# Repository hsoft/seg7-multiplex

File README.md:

# Multiplexed 7-segment display array

This board is a multiplexed array of 4 7-segment displays that receives its
input through a custom serial protocol. The board uses a USB-A connector to
connect `VCC`, `GND` and its two serial pins. It's multiplexed to minimize the
number of pins and ICs we need to use. We end up only needing an ATtiny45 and
2 ICs to drive the 4 displays.

The goal is to be able to offload the "digit display" complexity off little
devices I'm planning to do. Of course, there's tons of ready-to-use displays
out there but I'd like to explore simple and minimal designs.

I'm also hoping to have something that draws minimal current. My current
prototype (v3) works on 3V and draws about 7mA when it's not receiving data. For
reference, the backlight of a typical 2x8 LCD screen draws something like
20-40mA.

Click on the image below for a video:

## Serial protocol

It works by serially sending it 5 bits of data using `INSER` and `INCLK`, the
first 4 bits being an encoded digit from `0` to `9`. Each digit is sent
starting with the most significant bit. Before each digit, a single bit is sent
to indicate whether this digit has a dot. The first digit to be sent is the
least significant digit (the rightmost).

Before that, a single "empty" clock is sent to "wake" the MCU up and give it
time to put itself in "input" mode (that is, give it time to finish its current
refresh operation, if any).

The driver should wait 200us before the "wake up" trigger and the rest of the
data so that we have time to finish any ongoing display refresh operation.
after that, 50us between each clock should be enough.

Thus, to send "43.21", the bits to be sent would be:

    00100 (4)
    10011 (dot + 3)
    00010 (2)
    00001 (1)
    01010 (10, the checksum of 4 + 3 + 2 + 1)

This is done for each digit that needs to be shown (starting with the rightmost
digit). This means 20 bits.

Following that, we have a checksum which is the sum, in binary form, of the
sent digits. That sum is 5 bits long. It's not enough to hold the maximum value
(36) of that sum, but being 5 bits simplifies the code and is solid enough for
our purpose. Dot masks aren't checksummed.

If the checksum doesn't match the received number, the display shows an error
that can't be mistaken for a real number.

I could have gone for sending straight binary values instead of digits but I
thought it would be nice to eventually add support for special values (dash,
empty, etc)

The board itself takes care of properly refreshing the displays. We refresh one
display every 1ms, cycling over active displays. We only need to send new digits
when they change.

## Prototypes

### v1

My first prototype was using two shift registers to multiplex my 7-segments
digits. It worked rather well but my craftmanship was lacking. Soldering wasn't
good and the board was too cramped. I also forgot (or didn't know about) to add
decoupling capacitors next to my ICs and I think that this is why that prototype
wasn't working perfectly (it would receive the wrong data through serial and
would even sometimes have a corrupt display (missing/extra segment) about 10% of
the time). Also, to get that figure to 10% from 50%, I had to lower my serial
clock timing to 100us (a minimum of 100us between serial clocks). That seems a
bit high to me. Something is fishy.

As a software developer, I'm used to be on solid grounds. If the code is
logical, generally, things work. Here I have to learn to deal with timing and
power fluctuation issues. These present interesting challenges.

Because my board was too cramped, I needed to make a new prototype altogether
(with decoupling capacitors this time) and I thought that if I was going to do
that, I might as well try another design, that is, my v2.

You can see the code for this v1 in the `v1` branch of this repo. I have no
KiCAD schema though. Never bothered. Will do for v2 though.

### v2

Although I think that my design for v1 was globally sound, I think in
retrospective that the MCU did too many things. The less things the MCU does,
the more logic you offload to ICs, the more robust your design is going to be (I
think). After all, people designing ICs went through much more trouble to make
sure it worked well than I did for my prototype...

So that's why I went with a new multiplex design with 3 ICs:

1. 7-segment decoder hooked to my displays
2. binary counter hooked to the decoder
3. shift register hooked to displays' `VCC` (and `DP`)

With the decoder + counter, sending a particular digit mask to the display is
only a matter of clocking the counter, so it's only two pin changes. That is
much much less than the number of pins we have to change to send a particular
digit mask into a shift register.

I could use a decade counter to only cycle through the first 10 glyphs of my
decoder's 16, but as I looked as extra glyphs, I realized (I really wasn't sure
what they were supposed to be for initially) that they're probably optimized for
multiplexing, that is, that the 5 extra masks (last one is blank) are masks that
"fit" multiple digits. For example, the 11th mask is the lower half of `5` which
also fits 6 and 8.

Therefore, when cycling through masks, you can enable `VCC` not only for exact
digit matches but also partial matches and, in the end, you've refreshed your
multiplexed displays properly. I'm thinking that 1ms per cycle should be good
enough to keep us under the 10ms threshold (at which point the eye starts to see
a flicker) even if we cycle through 16 digit masks.

One problem though is that the 7-segments decoder doesn't handle `DP`, which I'd
like to support. This is why I'm thinking of bringing down (theoretical) digit
support from 8 to 4 and hook 4 pins of my shift register directly to my `DP`
pins. This way, I'll handle `DP` status completely outside of the multiplexing
process.

With the `ATtiny45`, I only have 3 free output pins (2 pins are used for serial
communication). That requires creativity to handle all my ICs with only 3 pins,
but I think I have a good idea:

1. pins 1 and 2 hooked to my shift register
2. pin 3 to my binary counter
3. pin 3 also hooked to my shift register's `OE` pin (output enable).

I need to control `OE` because there's always going to be a slight window of
time during which the decoder cycled and the shift register hasn't updated `VCC`
pin yet. If I let `OE` on, then my displays are going to have "ghost" branches.
The pin clocking the binary counter is going to be in position to enable `OE`
most of the time and right when we will toggle the binary counter clock, `OE`
will become disabled. Then, I'll update the shift register and toggle `OE` back
(which will not trigger a binary counter update since it takes a full on/off
cycle to trigger). I haven't looked yet whether I'm going to be needing an
inverter for this. If yes, I'll probably look for a shift register that allows
me to do that without an inverter (an extra IC just for this seem a bit much).

**Conclusion**: It went well! It was the first time I ordered a PCB from a
KiCAD design. Of course, I made some mistakes in it and a lot of cowboy
soldering was necessary to adjust, but in the end, I had a fully functional
prototype! Unlike v1, it received data properly and displayed it correctly!

However, I'm not done yet, I need a v3 because 3 ICs is too many: I'd like to
get this package in a 55mmx30mmx20mm enclosure. I'll need to go "double side"
and remove an IC.

### v3

With v3, I get rid of the counter. Instead of using 4 bits of the SR for DP,
I connect them to the BCD. Then, I connect SER to DP add a refresh "round"
especially for DP. This means that we generally have to keep SER high to avoid
falsely lighting DPs.

It still offloads most of the complexity to the BCD and gets rid of an IC.
Moreover, althrough I didn't experience it, I felt that the CNT approach was
flaky: the counter **had** to stay in sync with the MCU and the MCU had no way
to reset the counter to enforce syncing (not enough pins).

## Build

To build the software, you need:

* [AVRA][avra]
* [avrdude][avrdude] to send firmware to MCUs

You can build the resulting `seg7multiplex.S.hex` with `make` and send it to
the MCU through `avrdude` with `make send`.

## Simulation

This project can be run on a desktop computer through [simavr][simavr]. It 
produces a VCD file which can then be opened with [gtkwave][gtkwave].

You can compile the simulation with `make simulation` and then run the
resulting executable without parameters.

The simulation runs two MCUs at the same time. First, of course, the
`seg7multiplex` program, but also, on a separate virtual attiny45, the `drive`
program. It hooks them up together and let them run for 2 seconds.

The resulting gtkwave file is very insightful for debugging.

[avra]: http://avra.sourceforge.net/
[avrdude]: https://www.nongnu.org/avrdude/
[simavr]: https://github.com/buserror/simavr
[gtkwave]: http://gtkwave.sourceforge.net/

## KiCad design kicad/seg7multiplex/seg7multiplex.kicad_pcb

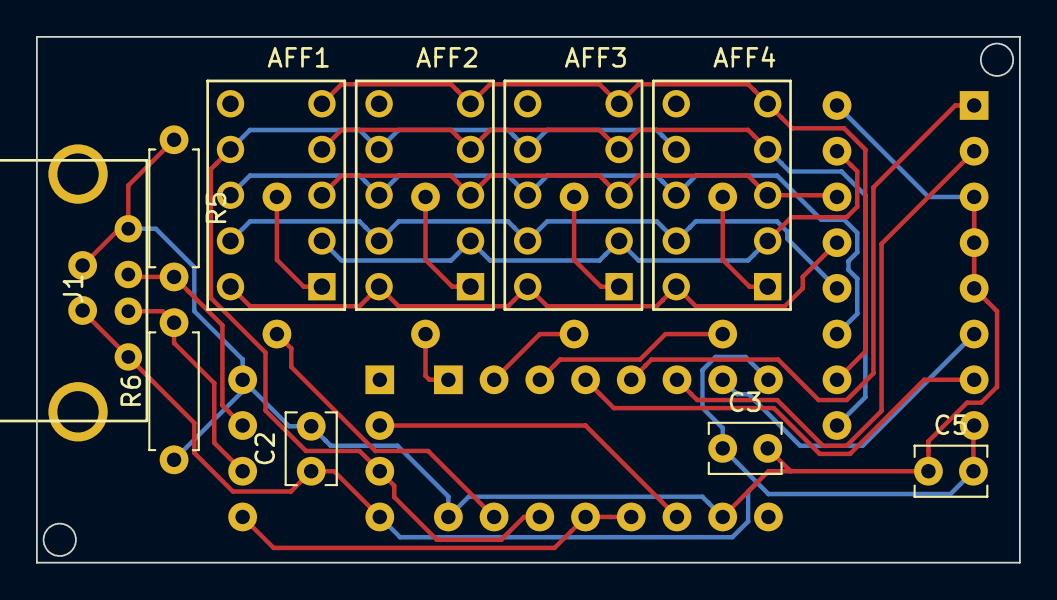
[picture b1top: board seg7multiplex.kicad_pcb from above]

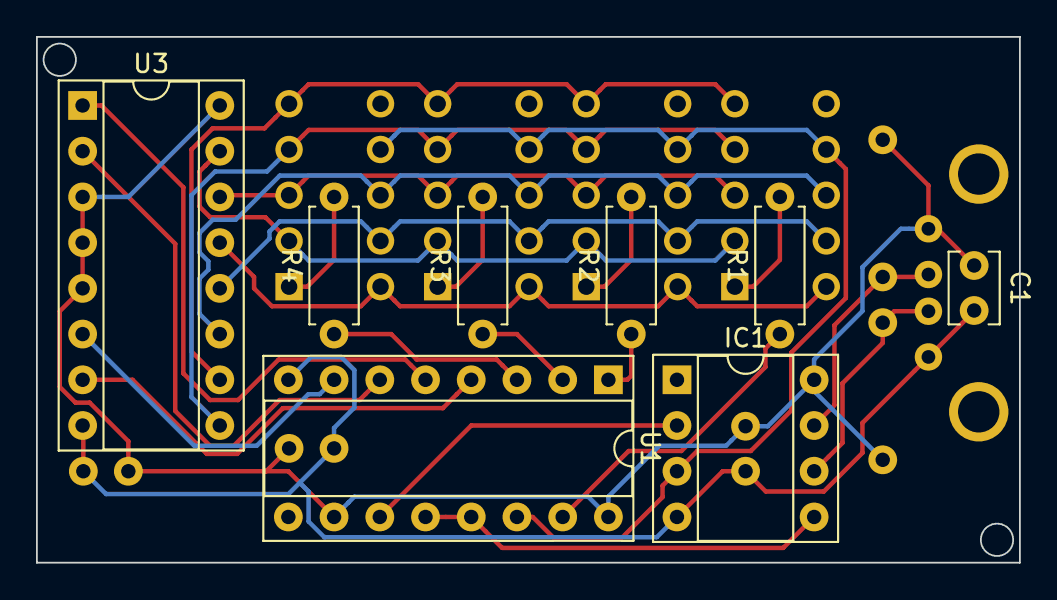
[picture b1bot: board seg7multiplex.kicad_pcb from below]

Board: 2 copper layers, 54.6 x 29.2 mm, 18 parts (8 on the bottom side), 26 nets.

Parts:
AFF1, AFF2, AFF3, AFF4: LSHD-A101
C1: 1uF; C_Disc_D3.8mm_W2.6mm_P2.50mm
C2, C3, C5: 0.1uF; C_Disc_D3.8mm_W2.6mm_P2.50mm
IC1: ATTINY45-P; DIP-8_W7.62mm_Socket
J1: USB_A; USB_A_Through
R1, R2, R3, R4: 110; R_Axial_DIN0207_L6.3mm_D2.5mm_P7.62mm_Horizontal
R5, R6: 10K; R_Axial_DIN0207_L6.3mm_D2.5mm_P7.62mm_Horizontal
U1: SN74HC595; DIP-16_W7.62mm_Socket
U3: 74LS48; DIP-16_W7.62mm_Socket

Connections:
/AFF1: R1.1, U1.15
/AFF2: R2.1, U1.1
/AFF3: R3.1, U1.2
/AFF4: R4.1, U1.3
/DECA: U1.4, U3.7
/DECB: U1.5, U3.1
/DECC: U1.6, U3.2
/DECD: U1.7, U3.6
/INCLK: IC1.7, J1.2, R5.2
/INSER: IC1.6, J1.3, R6.2
/RCLK: IC1.5, U1.12, U1.13
/SER_DP: AFF1.7, AFF2.7, AFF3.7, AFF4.7, IC1.3, U1.14
/SRCLK: IC1.2, U1.11
/a: AFF1.10, AFF2.10, AFF3.10, AFF4.10, U3.13
/b: AFF1.9, AFF2.9, AFF3.9, AFF4.9, U3.12
/c: AFF1.8, AFF2.8, AFF3.8, AFF4.8, U3.11
/d: AFF1.5, AFF2.5, AFF3.5, AFF4.5, U3.10
/e: AFF1.4, AFF2.4, AFF3.4, AFF4.4, U3.9
/f: AFF1.2, AFF2.2, AFF3.2, AFF4.2, U3.15
/g: AFF1.3, AFF2.3, AFF3.3, AFF4.3, U3.14
GND: C1.2, C2.1, C3.1, C5.2, IC1.4, J1.4, U1.8, U3.8
unnamed: AFF1.1, R1.2
unnamed: AFF2.1, R2.2
unnamed: AFF3.1, R3.2
unnamed: AFF4.1, R4.2
VCC: C1.1, C2.2, C3.2, C5.1, IC1.8, J1.1, R5.1, R6.1, U1.10, U1.16, U3.3, U3.4, U3.5, U3.16

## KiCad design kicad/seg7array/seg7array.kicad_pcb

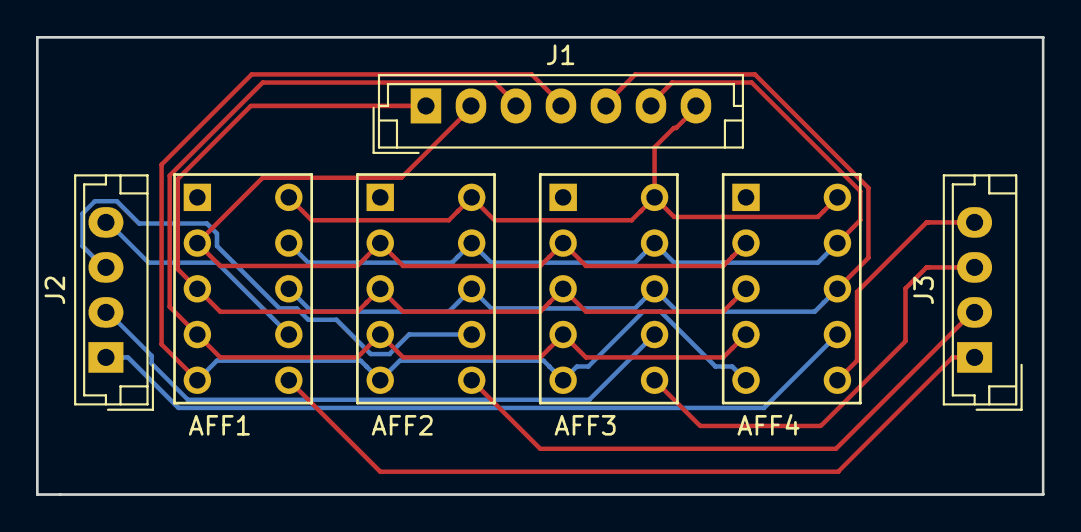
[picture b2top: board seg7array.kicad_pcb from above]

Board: 2 copper layers, 55.9 x 25.4 mm, 7 parts (0 on the bottom side), 15 nets.

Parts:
AFF1, AFF2, AFF3, AFF4: LSHD-A101
J1: Conn_01x07; JST_EH_B07B-EH-A_1x07_P2.50mm_Vertical
J2, J3: Conn_01x04; JST_EH_B04B-EH-A_1x04_P2.50mm_Vertical

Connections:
/a: AFF1.10, AFF2.10, AFF3.10, AFF4.10, J1.7
/b: AFF1.9, AFF2.9, AFF3.9, AFF4.9, J1.6
/c: AFF1.8, AFF2.8, AFF3.8, AFF4.8, J1.5
/d: AFF1.5, AFF2.5, AFF3.5, AFF4.5, J1.4
/e: AFF1.4, AFF2.4, AFF3.4, AFF4.4, J1.3
/f: AFF1.2, AFF2.2, AFF3.2, AFF4.2, J1.2
/g: AFF1.3, AFF2.3, AFF3.3, AFF4.3, J1.1
unnamed: AFF1.6, J3.1
unnamed: AFF1.7, J2.4
unnamed: AFF2.6, J3.2
unnamed: AFF2.7, J2.3
unnamed: AFF3.6, J3.3
unnamed: AFF3.7, J2.2
unnamed: AFF4.6, J3.4
unnamed: AFF4.7, J2.1

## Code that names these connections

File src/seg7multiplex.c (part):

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#include "../common/intmath.h"

// Clock pin of our shift register
#define SRCLK PinB3

/* SER_DP is wired to both our shift register (data pin) and the DP pin of
 * every display.
 *
 * We generally keep this pin HIGH to avoid lighting the dot on our displays.
 */
#define SER_DP PinB4

/* "Buffer clock" pin of the shift register. Also wired to OE.
 *
 * We generally want to keep this pin LOW so that outputs are enabled most of
 * the time.
 */
#define RCLK PinB0

// Input clock
#define INCLK PinB2

// Input data
#define INSER PinB1

#define MAX_SER_CYCLES_BEFORE_TIMEOUT 3
#define DIGITS 4
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 * display mask (the shift register's output is splitted in half: 4 bits for
 * the glyph and 4bits for the display mask) to our SN74HC595 shift register.
 *
 * The dot is displayed through SER_DP, which is wired to the DP pin of every
 * display. When we have a display_dotmask, we run a "blank glyph" run and set
 * SER_DP LOW (enabled) along with a display mask in the shift register to
 * specify which displays get the dot.
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            if (sr_sender.index == 7) {
                res = SRValueSenderStatus_Last;
            }
            pinset(SER_DP, sr_sender.val & (1 << (7 - sr_sender.index)));
            pinhigh(SRCLK);
            sr_sender.going_high = false;
            sr_sender.index++;
        } else {
            if (sr_sender.index == 0) {
                res = SRValueSenderStatus_Beginning;
            }
            pinlow(SRCLK);
            sr_sender.going_high = true;
        }
    } else {
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             * the SR, but it doesn't matter because the value that was there
             * before has just been invalidated.
             */
            pinhigh(RCLK);
            break;
        case SRValueSenderStatus_Middle:
            break;
        case SRValueSenderStatus_Last:
            // Only enable DP (low) during the DP round.
            pinset(SER_DP, current_glyph != BLANK_GLYPH);
            // Flush out the buffer with RCLK
            pinlow(RCLK); // OE enabled, but SR buffer isn't flushed
            _delay_us(1);
            pinhigh(RCLK); // SR buffer flushed, OE disabled
            _delay_us(1);
            pinlow(RCLK); // OE enabled
            break;
        case SRValueSenderStatus_Finished:
            res = false;
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        // first clocking is only to announce data. No actual data is recorded.
        input_mode = true;
    } else {
        serial_queue_write(pinishigh(INSER));
    }
}

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    sei();
#endif

    pinoutputmode(SER_DP);
    pinoutputmode(SRCLK);
    pinoutputmode(RCLK);
    // we generally keep SER_DP high to avoid lighting DP
    pinhigh(SER_DP);

    input_mode = false;
    serial_queue_init();
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
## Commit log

2017-09-21 Initial commit
    Began working on the simulation. Just one digit for now.
2017-09-21 Begin playing with multiplexing
    There's a glitch in seg7 representation during value increase/decrease
    but I haven't figured out what's the cause yet.
2017-09-22 Fix glitches in seg7 simulation display
    It now works pretty well with our two displays. The only "glitch" we can
    see sometimes is the leftover of the previous digit when increasing our
    value, but that's to be expected because that's how the LED fading logic
    works.
2017-09-22 Add a 3rd digit through a decoder and inverter
    For a reason I haven't yet figured out, when we hit the `300` value, the
    LED display goes to `044`. strange...
2017-09-22 Add ascii art!
2017-09-23 We now have 8 digits!!!
2017-09-26 Stop using PB5
    Will I ever learn that this pin cannot be used as IO? To free that pin,
    I've made the `SER` pin shared between inputs and outputs. Works in
    simulation...
2017-10-23 Adapt to the upcoming icemu v0.3
2017-10-24 Fix broken non-sim build
2017-10-24 Fix inverted B2 and B3 pins
    The wiring of the prototype wasn't the same as in the simulation. But as
    of now, we know that the "display" part of code works on the prototype (it
    has, however, only 3 digits)! The serial input hasn't been tested yet.
2017-10-28 Make MAX_DIGITS configurable
    Also, deduplicate Makefile contents.
2017-10-30 sim: extract SerialInput from Circuit
    Also, use new `enable_interrupt_on_pin()` MCU method.
2017-10-30 sim: make UI optional
    This will make embedding the sim into another project easier.
2017-10-31 sim: use add_chip() on seg7 displays
2017-10-31 sim: small tweaks so that I can embed the project in another one
2017-11-02 Update icemu to make sim much faster
2017-11-04 Adapt code so it works with my new prototype
    I've scrapped my old prototype to make a new one that fits in a small
    box. The way wiring is done in this new prototype requires that I change
    my code.
    Also, add a new `--ftdi` option to the simulator!
2017-11-08 Big refactoring: make display refreshing routine more atomic
    My serial input routine was too heavy for its own good and I had to
    rethink the whole process. See comment in seg7multiplex.c
    This works in simulation, haven't tried on my prototype yet.
2017-11-10 Still trying to make things work
    My previous approach didn't work on the prototype, `SER` still got
    confused all the time. Now instead of having a fine-grained "lock" on
    `SER`'s input/output mode, I'm trying a more coarse-grained approach
    with `input_mode`.
    Here, we begin each serial session with a single "empty" `INCLK` rising
    edge that tells the MCU to stop all display refreshing activity. The MCU
2017-11-10 Give INSER its own pin
    The idea of sharing the `SER` pin with `INSER` was a bad idea. It might
    be possible to make it work, but its over my current skill level.
    `SR1`'s `RCLK` had its own pin, so I took it out and hard-wired it to
    `SRCLK`. That makes the seg7 output code a bit uglier, but it frees a
    pin.
    This works on the prototype! finally!
2017-11-26 Use the new C rewrite of icemu
2017-11-29 Update icemu
2017-11-30 sim: extract circuit in a separate unit
    This will make integration in other projects easier.
2017-12-07 Add FTDI support to drive serial input of the real prototype!
    And it works! I have a functional prototype!
2018-02-23 Begin writing a test bench
2018-02-24 input: fix timeout falsely being triggered half the time
2018-02-26 Fix dash character mask
2018-02-26 Indicate serial errors through leftmost dot
2018-03-15 Planning out v2 of my prototype
2018-03-19 Add KiCAD schema
2018-03-25 Update code and simulation to the v2 prototype
    Once a couple of kinks in `icemu` were fixed, works surprisely well,
    with serial input code untouched and all.
    `DP` is not implemented yet.
2018-03-25 Implement dot displaying logic
2018-03-25 Fix sim keybinding label
2018-03-25 Update asciinema demo
2018-09-07 Update to Kicad 5
2018-09-07 Try to associate some footprints to components
2018-09-08 Add USB connector to schema and generate netlist
2018-09-13 Add new kicad "seg7array" project
2018-09-18 kicad: add seg7multiplex footprint
2018-10-08 Adjustment after first prototype revision
    I've received my first KiCAD-designed PCB! After a few cowboy adjustments
    (soldering stuff here and there), I could manage to make the thing work!
    But it flickered badly, so I had to heavily optimize my multiplexing
    algo to make flickering go away. As it is right now, and with
    modification to my KiCAD design (which have been done manually on my
    PCB to confirm soundness), I get a display that displays stuff correctly
2018-10-08 It works perfectly!!!
    After some sizeable messing around, I could finally make the prototype
    work perfrectly! I mean: the serial protocol works without a hitch, the
    proper digits get there 100% of the time! No flickering!
    One time cnosuming problem I had was that my FT232H controller I use
    for testing has a 5V power supply, but 3V logic (it outputs 3V to its
    data pins). It took me a while to realise that. Things weren't working
2018-10-09 Fix local project library paths
2018-10-24 Reverse digits
    Bullseye! I received my PCB for this 3rd prototype, I solder it, power
    it up, it works perfectly on the first try! No flickering, displaying
    what it should... Except that the digits were reversed.
    I haven't tried USB communication yet though...
    So now I have this tight PCB that almost fits (U3 it too close to the
    screw socket, it doesn't fit quite right. But it's no big deal, I have
2019-01-12 Update comments
2019-01-12 Fix spurious DP display
    Things worked well on simulation, but on the real thing, I would have my
    DP lighting all the time, with the lighting level slightly differing
    depending on the displayed glyph.
    When designing the code, I thought that SER_DP briefly flickering when
    sending data to the SR wouldn't significantly light DP because it was a
    very small portion of the overall "SER_DP" position, which was, in the
2019-01-15 Add debug mode on MCU
2019-01-15 sim: improve FTDI logic
2019-01-15 Reverse digits (again)
    It seems that I've turned my displays around without noticing in my
    latest prototype.
    But otherwise, I now have a prototype that work very well! It properly
    receives input from FTDI, doesn't flicker and the board didn't need any
    modification!
    The only problem is that the board is a *tiny bit* too large on a corner
2019-01-15 Add "drive" subproject
    Work well (see README), but sometimes I get a wrong digit in,
    something I didn't get on FTDI. Strange...
2019-01-31 Make error condition more easily visible
    Also, cycle through digits rather than glyphs. Seems less MCU-intensive
    and results in simpler code when introducing the use of ERROR_GLYPH.
2019-01-31 Merge digit_count into current_digit
    Since they're never used in the same mode, we can save one precious
    byte!
2019-01-31 Add checksum digit to communication protocol
    My prototype was sometimes (but rarely), receiving the wrong number. I'm
    not sure if it's due to bad soldering in my USB wire or voltage
    irregularities or whatever else, but if I'm going to use those readings
    for anything important, I have to be able to trust the the number
    displayed is the good one.
2019-02-06 Move serial comm code to avr-common
2019-02-19 Begin conversion to ASM
2019-02-19 Add DP support
2019-02-20 Improve documentation
2019-02-20 sim: bring in the driver!
    First steps into allowing the simulation of a seg7 driver at the same
    time as the seg7 itself.
2019-02-20 Begin implementing input mode
    For now, input mode is nothing more than "don't refresh displays until
    timeout", but it's nice to see it work in gtkwave...
    This whole simavr+gtkwave thing works very well!
2019-02-22 Use AVRA for compiling instead of avr-gcc
    I like AVRA better than binutils's `avr-as` because it's simpler, more
    self-contained, and also, it tries to mimick `avrasm`, which allows me
    to write assembler code that is more in line with what a majority of
    other AVR users write.
2019-02-23 Fix offset bug
    Under avr-gcc, jump offsets were in bytes, under AVRA, it's in number of
    instructions.
    My SENDSR loop has been messed up by the migration to AVRA because of
    this.
2019-02-23 Implement input mode in assembler
    Works well in simulation for the first sent digit group (2345). It
    seems that subsequent digit groups trigger error condition. To examine.
    But otherwise, I'm still really happy with how simavr/gtkwave debugging
    works out. Very easy to debug tricky situations.
    My eyes are getting used to decode binary out of two CLK/SER tracks :)
2019-02-23 Fix checksum sent in wrong order by the driver
2019-02-24 Rewrite driver in asm
2019-02-24 Execute INPT_ERROR on input timeout
    Otherwise, we get corrupt display on timeouts rather than clear error
    display.
2019-02-24 Remove old C code
2019-03-28 Upgrade to avra 1.4
2019-03-28 Limit checksum to 5 bits
    This way, we can validate inputs like 9999.
2019-03-28 Add video link to README
